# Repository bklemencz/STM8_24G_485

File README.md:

# STM8_24G_485

STM8S103 Milight 2.4Ghz Remote to RS485

Uses LT8900 series 2.4G tranceivers

Additional settings possible on 2.4G, protocol desciption in 
https://github.com/bklemencz/Motion_Node/tree/master/FW

Hardware is based on STM8S103 Minimum Dev Boards, PCB is single layer.

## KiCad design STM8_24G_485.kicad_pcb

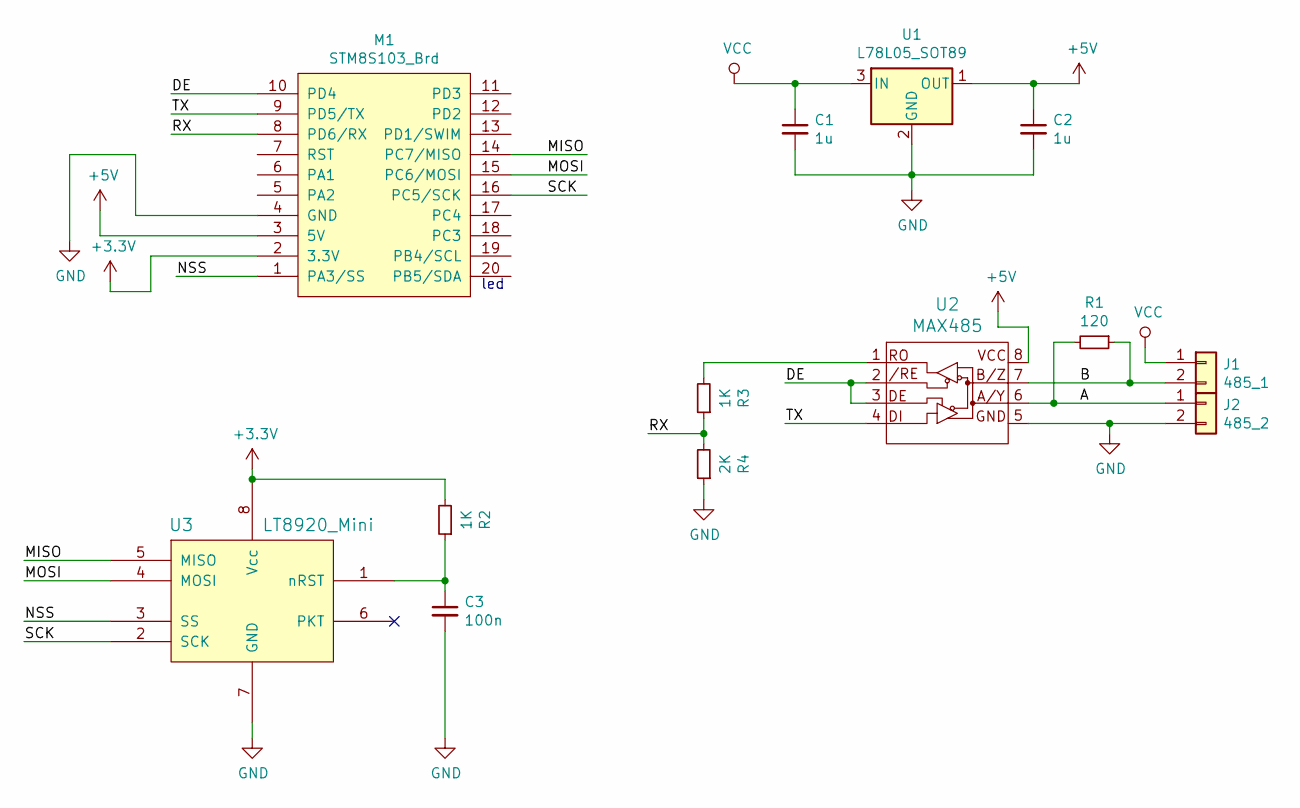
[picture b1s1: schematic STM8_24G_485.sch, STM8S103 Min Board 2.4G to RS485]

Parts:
C1, C2: 1u; C_0805
C3: 100n; C_0805
J1: 485_1; TerminalBlock_Phoenix_PT-1,5-2-3.5-H_1x02_P3.50mm_Horizontal
J2: 485_2; TerminalBlock_Phoenix_PT-1,5-2-3.5-H_1x02_P3.50mm_Horizontal
M1: STM8S103_Brd; STM8S103_Minimum_Board
R1: 120; R_0805
R2, R3: 1K; R_0805
R4: 2K; R_0805
U1: L78L05_SOT89; SOT-89-3
U2: MAX485; SOIC-8_3.9x4.9mm_Pitch1.27mm
U3: LT8920_Mini; XY-WB_LT8920_Nosilk

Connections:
+3V3: M1.2 (3.3V), R2.2, U3.8 (Vcc)
+5V: C2.1, M1.3 (5V), U1.1 (OUT), U2.8 (VCC)
/A: J2.1, R1.2, U2.6 (A/Y)
/B: J1.2, R1.1, U2.7 (B/Z)
/DE: M1.10 (PD4), U2.2 (/RE), U2.3 (DE)
/MISO: M1.14 (PC7/MISO), U3.5 (MISO)
/MOSI: M1.15 (PC6/MOSI), U3.4 (MOSI)
/NSS: M1.1 (PA3/SS), U3.3 (SS)
/RX: M1.8 (PD6/RX), R3.1, R4.2
/SCK: M1.16 (PC5/SCK), U3.2 (SCK)
/TX: M1.9 (PD5/TX), U2.4 (DI)
GND: C1.2, C2.2, C3.2, J2.2, M1.4 (GND), R4.1, U1.2 (GND), U2.5 (GND), U3.7 (GND)
unnamed: C3.1, R2.1, U3.1 (nRST)
unnamed: R3.2, U2.1 (RO)
VCC: C1.1, J1.1, U1.3 (IN)

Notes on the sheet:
led

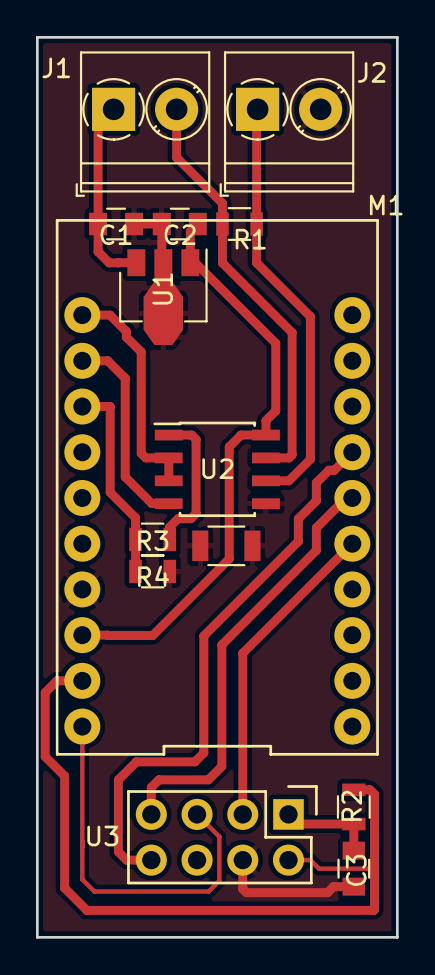
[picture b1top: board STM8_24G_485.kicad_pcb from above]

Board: 2 copper layers, 20.0 x 50.0 mm, 13 parts (0 on the bottom side), 15 nets.
